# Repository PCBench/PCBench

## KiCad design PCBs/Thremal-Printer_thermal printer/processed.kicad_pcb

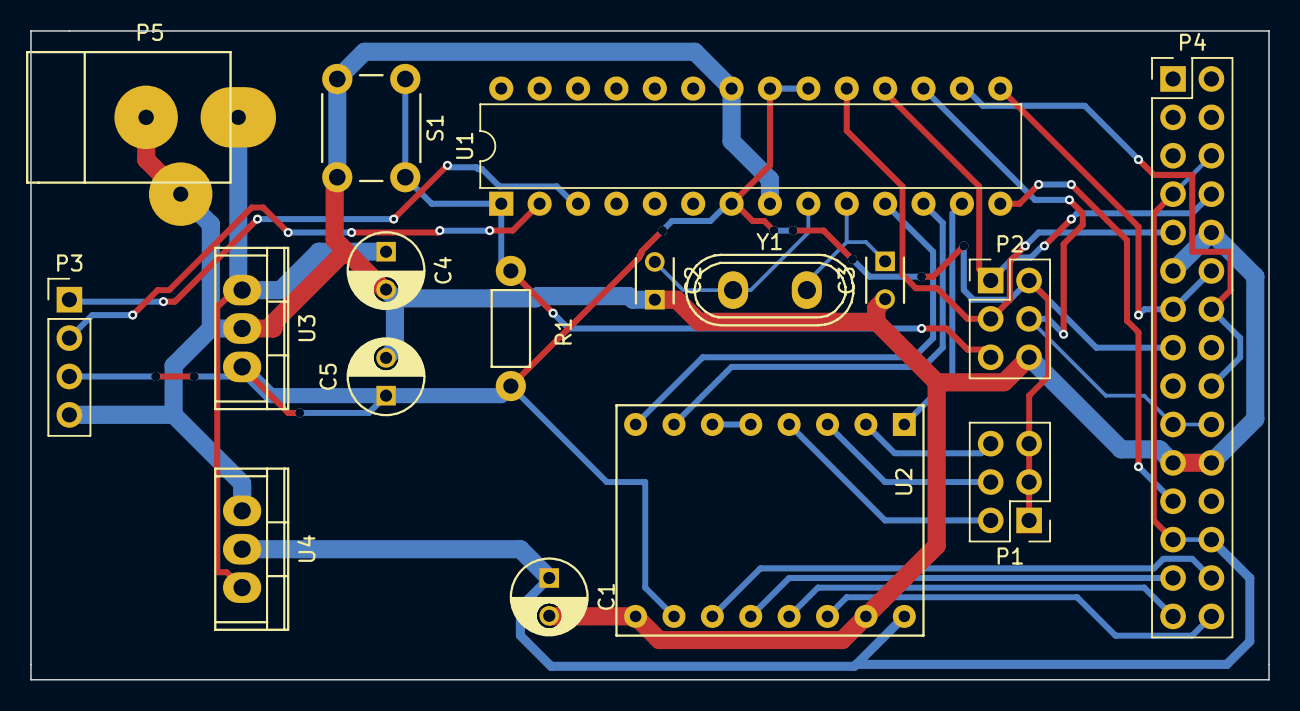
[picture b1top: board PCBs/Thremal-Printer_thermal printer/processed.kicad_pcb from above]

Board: 2 copper layers, 81.9 x 42.9 mm, 17 parts (0 on the bottom side), 26 nets.

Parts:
C1: 100uF; C_Radial_D5_L6_P2.5
C2, C3: 100nF; C_Disc_D3_P2.5
C4, C5: CP1_Small; C_Radial_D5_L6_P2.5
P1, P2: CONN_02X03; Pin_Header_Straight_2x03_Pitch2.54mm
P3: CONN_01X04; Pin_Header_Straight_1x04_Pitch2.54mm
P4: CONN_02X15; Pin_Header_Straight_2x15_Pitch2.54mm
P5: BARREL_JACK; PowerJack
R1: 10K; Resistor_Horizontal_RM7mm
S1: Switch; SW_PUSH_6mm
U1: ATMEGA328-P; DIP-28_W7.62mm
U2: A4988_pololu; SO16
U3: LM7805CT; TO-220
U4: LM317AT; TO-220
Y1: 16MHz; Crystal_HC50-U_Vertical

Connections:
/CLOCK: P2.3, P4.9, U1.19
/DATA: P2.1, P4.8, U1.18
/LATCH: P4.23, U1.14
/M1A: P4.27, U2.12
/M1B: P4.28, U2.11
/M2A: P4.29, U2.13
/M2B: P4.30, U2.14
/MOSI: P2.4, P4.19, P4.20, U1.17
/M_DIR: U1.11, U2.8
/M_ENABLE: U1.13, U2.1
/M_STEP: U1.12, U2.7
/RESET: P2.5, R1.1, S1.1, U1.1
/RX: P3.2, U1.2
/STROKE3-4: P4.14, P4.18, U1.16
/STROKE5-6: P4.12, P4.13, U1.15
/TX: P3.1, U1.3
GNDA: C1.2, C2.1, C3.2, C4.2, C5.2, P2.6, P3.4, P4.10, P4.11, P4.21, P4.22, P5.2, P5.3, S1.2, U1.8, U1.22, U2.9, U2.15, U3.2, U4.1
unnamed: C2.2, U1.9, Y1.2
unnamed: C3.1, U1.10, Y1.1
unnamed: P1.2, U2.4
unnamed: P1.4, U2.3
unnamed: P1.6, U2.2
unnamed: U2.5, U2.6
VCC: C4.1, P5.1, U3.1, U4.3
VDD: C5.1, P1.1, P1.3, P1.5, P2.2, P3.3, P4.15, R1.2, U1.7, U1.20, U1.21, U2.10, U3.3
VDDA: C1.1, P4.6, P4.7, P4.25, P4.26, U2.16, U4.2

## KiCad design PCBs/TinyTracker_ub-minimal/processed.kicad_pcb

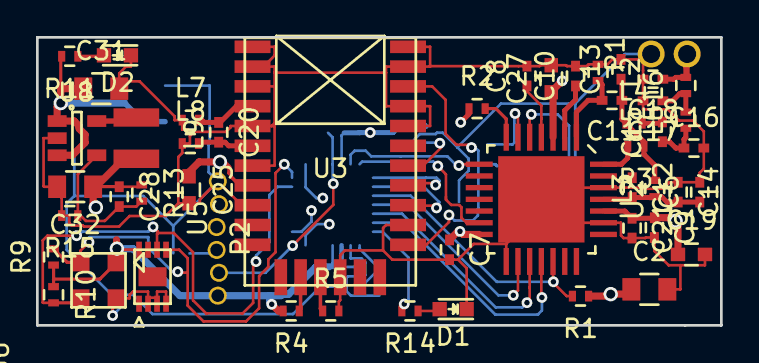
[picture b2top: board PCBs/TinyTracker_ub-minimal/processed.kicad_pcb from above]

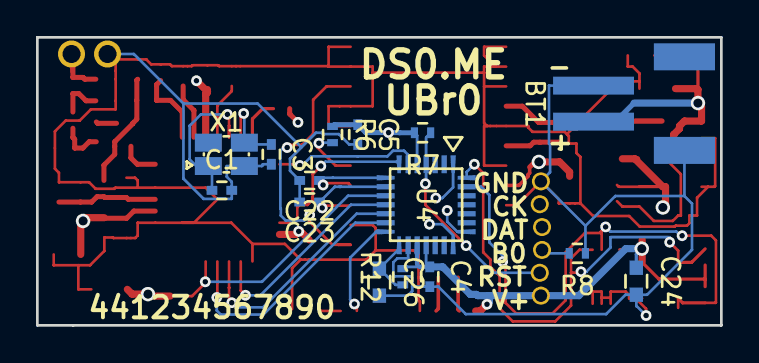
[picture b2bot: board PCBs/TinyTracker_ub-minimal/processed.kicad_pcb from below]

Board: 4 copper layers, 38.0 x 16.0 mm, 65 parts (15 on the bottom side), 42 nets.

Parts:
BT1: LiPoly; S2B-PH-SM4-TB
C1, C3: 10p; C_0402
C2, C32: 10u; C_0805
C4, C5, C7, C8, C10: 100n; C_0402
C6: 10n; C_0402
C9, C12, C15: 47p; C_0402
C11: *2.2p; C_0402
C13: 6.8p; C_0402
C14: 100p; C_0402
C16: 15p; C_0402
C17: 12p; C_0402
C18: 4.7p; C_0402
C19: 2.2u; C_0603
C20: 18p; C_0402
C21, C22, C23: 22p; C_0402
C24, C25, C26, C27: 1u; C_0603
C28: 8.2p; C_0402
C31: 4.7u; C_0805
D1: RED; LED-0603
D2: GREEN; LED-0603
L2: *18nH; R_0402
L3: 47nH; R_0402
L4: 22n; R_0402
L5: 12n; R_0402
L6: 18n; R_0402
L7, L8: DNP; R_0402
L9: 74479787222; Neosid_Inductor_SM-NE29_SMD1008
P1: ANT; ANT_50ohm
P2: CONN_01X06; 6-1.27mm
R1, R2, R4, R5, R6, R9, R10: 10k; R_0402
R3: 0; R_0402
R7, R8, R12, R15: 100k; R_0402
R11: 2.2k; R_0402
R13: 300k; R_0402
R14: 220; R_0402
U2: SX1276; QFP_28_0.65
U3: M10478; M10748
U4: STM32F048GUx; UFQFPN28
U5: CAT24M01; UDFN8
U6: MS5637
U8: LM3671; SOT-23-5
X1: 32M; XTAL-2x2.5

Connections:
+1V8: C2.1, C4.1, C5.1, C7.1, C9.1, C19.1, C21.1, C24.1, C25.1, C27.1, C28.1, C32.1, L9.2, P2.1, R1.1, R2.1, R4.2, R6.1, R7.2, R9.1, R10.1, R12.2, R13.1, U2.3, U2.14, U2.24, U3.8, U4.5, U4.17, U4.18, U5.8, U6.1
+BATT: BT1.1, C31.1, R11.2, U8.1, U8.3
/LORA TX/ANT: C18.1, L6.2, P1.2
/LORA TX/DIO0: U2.8, U4.6
/LORA TX/DIO5: U2.13, U4.7
/LORA TX/MISO: U2.17, U4.12
/LORA TX/MOSI: U2.18, U4.13
/LORA TX/SCK: U2.16, U4.11
/MCU/GPS_RX: C23.1, U3.20, U4.9
/MCU/GPS_TX: C22.1, U3.21, U4.8
/MCU/I2C_SCL: R10.2, U4.27, U5.6, U6.3
/MCU/I2C_SDA: R9.2, U4.28, U5.5, U6.2
/MCU/LORA_~CS: R1.2, U2.19, U4.10
GND: BT1.2, C1.2, C2.2, C3.2, C4.2, C5.2, C6.2, C7.2, C8.2, C9.2, C10.2, C12.1, C13.2, C14.1, C16.2, C17.2, C18.2, C19.2, C21.2, C22.2, C23.2, C24.2, C25.2, C26.2, C27.2, C31.2, C32.2, D1.1, D2.1, L2.1, L7.1, L8.1, P1.3, P2.6, R5.2, R8.1, R15.2, U2.15, U2.23, U2.26, U2.29, U3.1, U3.2, U3.3, U3.5, U3.7, U3.9, U3.15, U3.19, U3.24, U3.25, U3.27, U3.28, U4.16, U5.2, U5.3, U5.4, U6.4, U8.2, X1.3
unnamed: C1.1, U2.5, X1.1
unnamed: C3.1, U2.6, X1.2
unnamed: C8.1, U2.4
unnamed: C10.1, U2.2
unnamed: C11.1, C13.1, L3.2, L4.1, R3.1
unnamed: C11.2, L2.2, U2.1
unnamed: C6.1, C12.2, C14.2, L3.1, U2.25
unnamed: C15.1, C16.1, L5.1
unnamed: C15.2, L4.2
unnamed: C17.1, L5.2, L6.1
unnamed: C20.1, L7.2, U3.4
unnamed: C20.2, L8.2, U3.6
unnamed: C26.1, R12.1, U4.15
unnamed: C28.2, R13.2, R15.1, U8.4
unnamed: D1.2, R14.1
unnamed: D2.2, R11.1
unnamed: L9.1, U8.5
unnamed: P2.2, R7.1, U4.4
unnamed: P2.3, R8.2, U4.1
unnamed: P2.4, U4.21
unnamed: P2.5, U4.22
unnamed: R2.2, U2.7
unnamed: R3.2, U2.28
unnamed: R4.1, U3.13
unnamed: R5.1, U3.14
unnamed: R6.2, U3.22
unnamed: R14.2, U4.14
unnamed: U3.18, U3.26

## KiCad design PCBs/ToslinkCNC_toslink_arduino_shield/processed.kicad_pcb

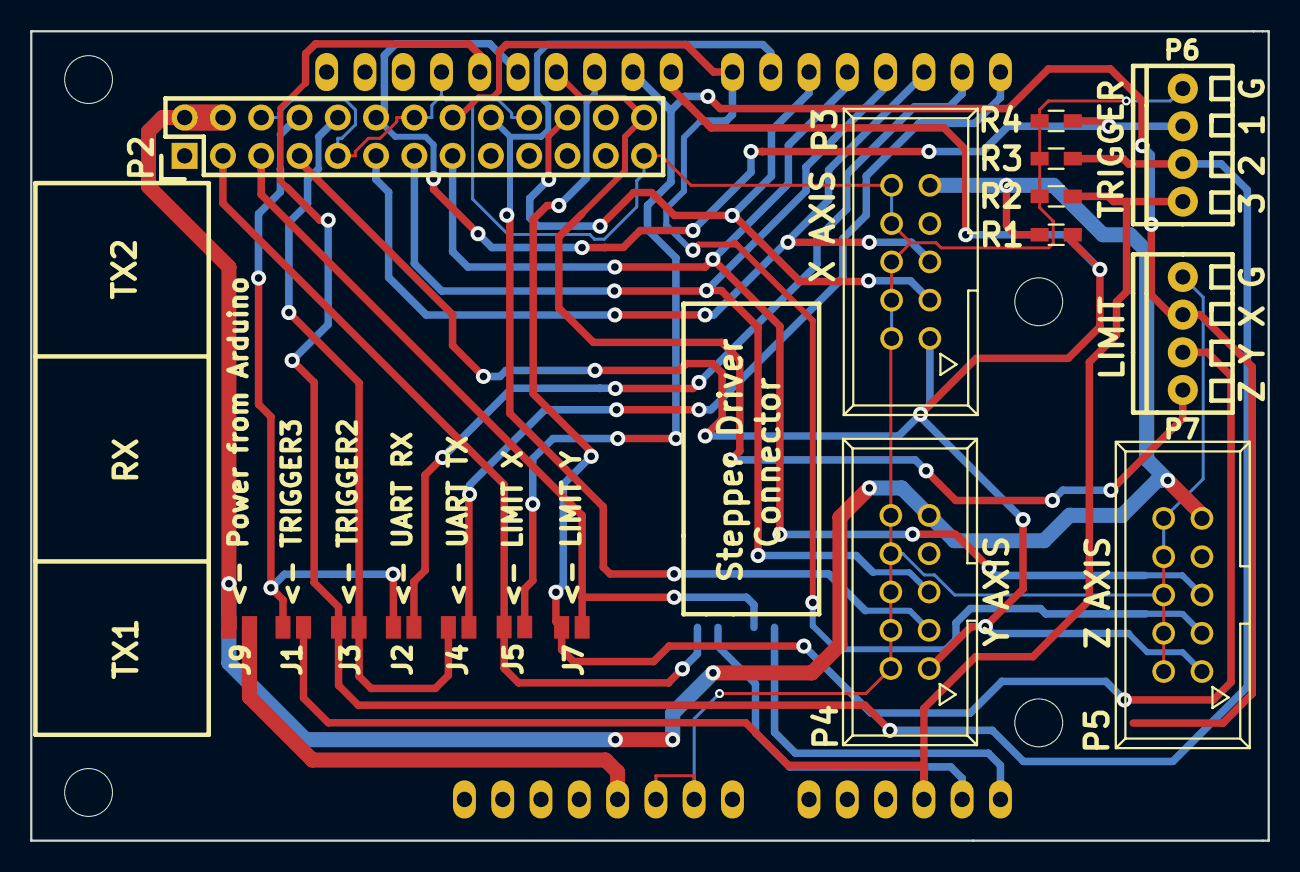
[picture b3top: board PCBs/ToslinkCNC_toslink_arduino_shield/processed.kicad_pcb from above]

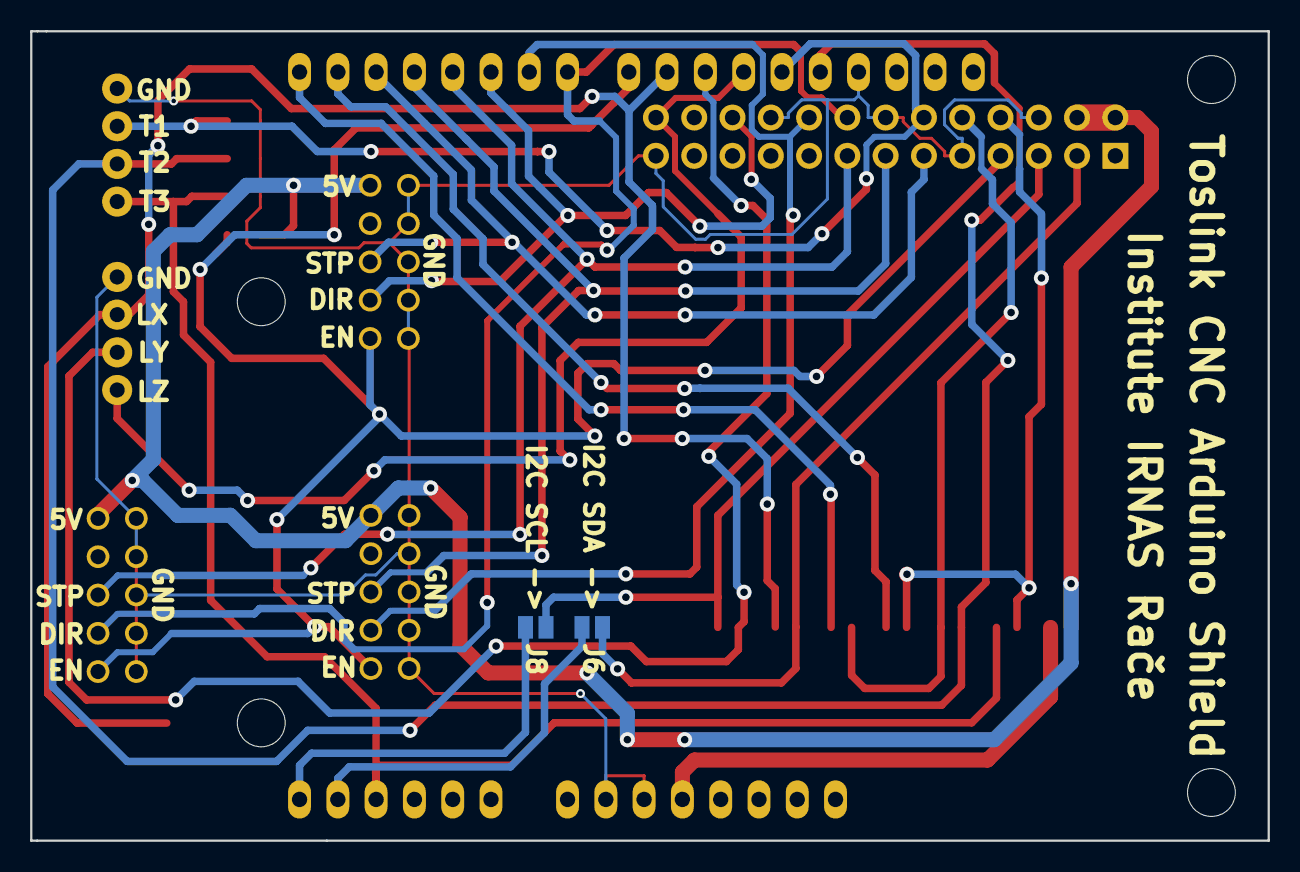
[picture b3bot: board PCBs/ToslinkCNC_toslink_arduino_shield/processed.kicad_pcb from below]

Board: 2 copper layers, 82.1 x 53.7 mm, 20 parts (2 on the bottom side), 24 nets.

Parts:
J1, J2, J3, J4, J5, J6, J7, J8, J9: solder_bridge
P1: Arduino UNO; ARDUINO_SHIELD
P2: Toslink CNC Transciever; toslink_pcb
P3, P4, P5: PoStep25-32_connector; VASCH5x2
P6, P7: CONN_01X04; terminal_block_2_5mm_4pole
R1, R2, R3, R4: 10K; R_0603_HandSoldering

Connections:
+5V: J9.2, P2.2, P2.4, P3.9, P4.9, P5.9, R1.1
DIR_X: P1.5, P2.22, P3.3
DIR_Y: P1.6, P2.18, P4.3
DIR_Z: P1.7, P2.16, P5.3
ENABLE: P1.8, P2.7, P3.1, P4.1, P5.1, R1.2
GND: P1.GND1, P1.GND2, P1.GND3, P2.6, P2.9, P2.14, P2.20, P2.25, P3.2, P3.4, P3.6, P3.8, P3.10, P4.2, P4.4, P4.6, P4.8, P4.10, P5.2, P5.4, P5.6, P5.8, P5.10, P6.4, P7.4, R2.1, R3.1, R4.1
I2C_SCL: J8.2, P1.AD5
I2C_SDA: J6.2, P1.AD4
LIMIT_X: J5.2, P1.9, P7.3
LIMIT_X/I2C_SDA: J5.1, J6.1, P2.3
LIMIT_Y: J7.2, P1.10, P7.2
LIMIT_Y/I2C_SCL: J7.1, J8.1, P2.5
LIMIT_Z: P1.11, P2.26, P7.1
POWER: J9.1, P1.5V
STEP_X: P1.2, P2.11, P3.5
STEP_Y: P1.3, P2.13, P4.5
STEP_Z: P1.4, P2.15, P5.5
TRIGGER1: P1.12, P2.12, P6.3, R4.2
TRIGGER2: J3.2, P1.13, P6.2, R3.2
TRIGGER2/UART_TX: J3.1, J4.1, P2.10
TRIGGER3: J1.2, P1.AD3, P6.1, R2.2
TRIGGER3/UART_RX: J1.1, J2.1, P2.8
UART_RX: J2.2, P1.1
UART_TX: J4.2, P1.0

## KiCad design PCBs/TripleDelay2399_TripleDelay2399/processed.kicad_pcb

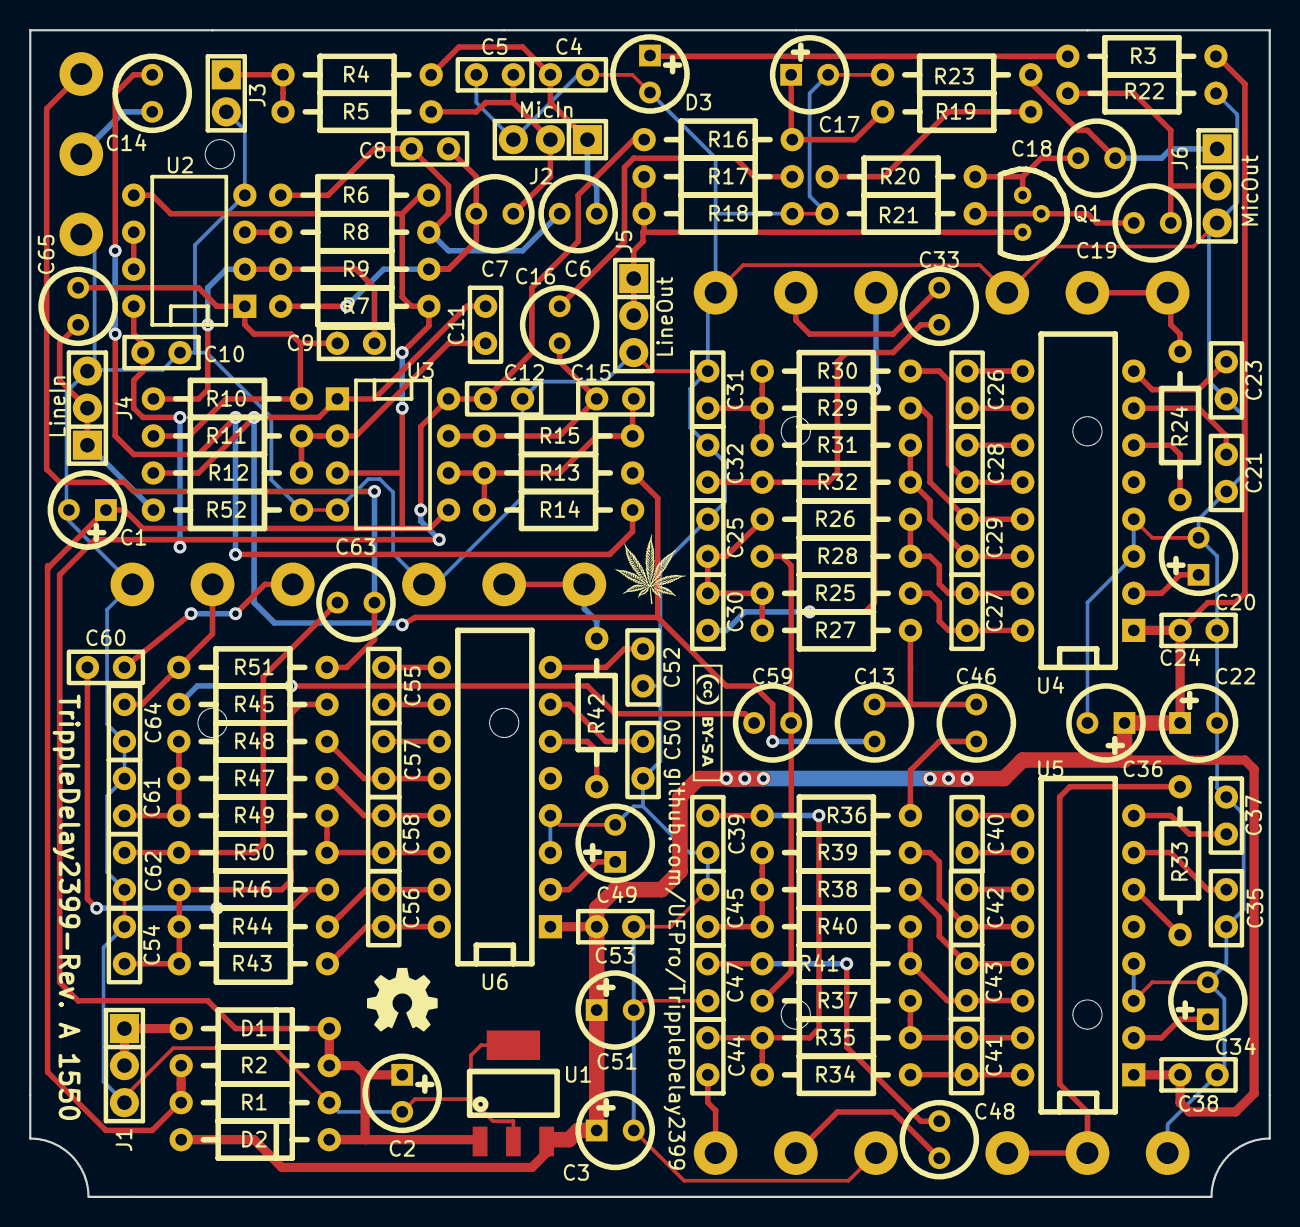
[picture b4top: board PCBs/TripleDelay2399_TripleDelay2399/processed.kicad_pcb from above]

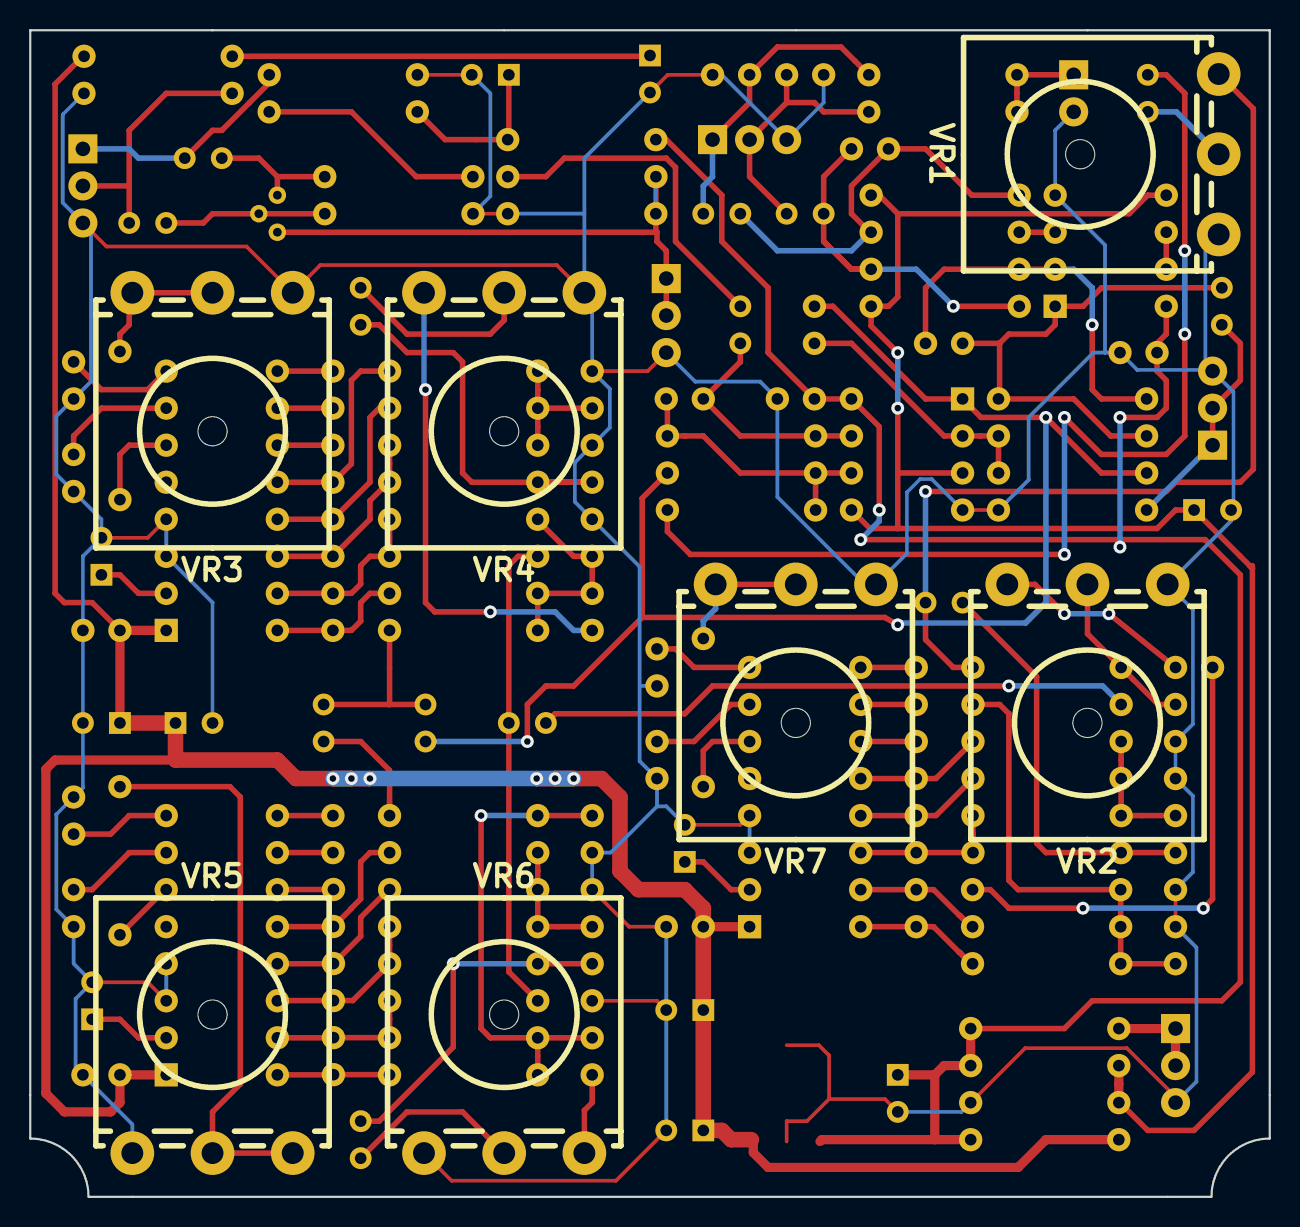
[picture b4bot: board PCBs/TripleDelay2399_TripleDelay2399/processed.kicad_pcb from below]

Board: 2 copper layers, 85.0 x 80.0 mm, 157 parts (7 on the bottom side), 90 nets.

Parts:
C1, C3, C17, C20, C22, C34, C36, C49, C51: 47µ; C_round-radial-polar-2,5mm-5mm
C2: 100µ; C_round-radial-polar-2,5mm-5mm
C4, C5: 100p; C_rect-radial-bipolar-100mil-2x5mm
C6, C7, C18, C19: 10µ; C_round-radial-bipolar-2,5mm-5mm
C8: 470p; C_rect-radial-bipolar-100mil-2x5mm
C9, C11, C15: optional; C_rect-radial-bipolar-100mil-2x5mm
C10, C12, C21, C23, C24, C26, C28, C35, C37, C38, C40, C42, C50, C52, C53, C55, C57: 100n; C_rect-radial-bipolar-100mil-2x5mm
C13, C14, C33, C46, C48, C59, C63: 1µ; C_round-radial-bipolar-2,5mm-5mm
C16: 4µ7; C_round-radial-bipolar-2,5mm-5mm
C25, C39, C54: 4n7; C_rect-radial-bipolar-100mil-2x5mm
C27, C29, C41, C43, C56, C58: 1n; C_rect-radial-bipolar-100mil-2x5mm
C30, C44, C60: 22n; C_rect-radial-bipolar-100mil-2x5mm
C31, C45, C61, C64: 47n; C_rect-radial-bipolar-100mil-2x5mm
C32, C47, C62: 10n; C_rect-radial-bipolar-100mil-2x5mm
C65: optional; C_round-radial-bipolar-2,5mm-5mm
D1, D2: 1N4001; D_axial_400mil
D3: blue; C_round-radial-polar-2,5mm-5mm
Des*: Val*; Pad-TH-0,8mm-1,6mm
Des*_2, Des*_3, Des*_4, Des*_5, Des*_6, Des*_7, Des*_8: Val*; MountingHole-3,2mm
Des*_9, Des*_10, Des*_11, Des*_12, Des*_13, Des*_14: Val*; Pad-TH-0,8mm-1,6mm
J1: DCIn; PinArray-100mil-1x3
J2: MicIn; PinArray-100mil-1x3
J3: P48; PinArray-100mil-1x2
J4: LineIn; PinArray-100mil-1x3
J5: LineOut; PinArray-100mil-1x3
J6: MicOut; PinArray-100mil-1x3
Q1: J112; TO-92_staggered-narrow
R1, R2, R8, R9, R11, R18, R25, R26, R27, R29, R30, R34, R35, R36, R38, R39, R43, R44, R45, R47, R48: 10k; R_axial_400mil
R3, R16, R32, R41, R50: 1k; R_axial_400mil
R4, R5, R22, R23: 6k8; R_axial_400mil
R6, R7: 4k7; R_axial_400mil
R10, R12: 180k; R_axial_400mil
R13, R14: 39k; R_axial_400mil
R15: 910; R_axial_400mil
R17, R21: 100k; R_axial_400mil
R19: 56k; R_axial_400mil
R20: 43k; R_axial_400mil
R24, R33, R42: 2k7; R_axial_400mil
R28, R37, R46: 5k1; R_axial_400mil
R31, R40, R49: 20k; R_axial_400mil
R51: 2k; R_axial_400mil
R52: optional; R_axial_400mil
U1: MCP1755S-5002; SOT223-3
U2, U3: NE5532; DIP-8_300
U4, U5, U6: PT2399; DIP-16_300
VAL: REF; CC-BY-SA08mm
VAL_2: REF; hempleaf5mm.mod
VAL_3: REF; oshw5mm
VR1, VR2, VR3, VR4, VR5, VR6, VR7: 50k lin; VR_potentiometer-piher-topmount_narrow-pins

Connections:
+4V5: C1.1, R1.1, R2.1, R6.1, R7.1, U2.5, U3.3, U3.5
+5V: C3.1, C22.1, C24.2, C36.1, C38.2, C51.1, C53.2, D2.1, R3.1, U1.3, U4.1, U5.1, U6.1
+9V: C2.1, C10.1, C12.1, D1.2, D2.2, R2.2, R16.1, U1.1, U2.8, U3.8
DLY_A-B: C59.2, R28.2, R37.2
DRY: C13.2, C46.2, R27.2
GND: C1.2, C2.2, C3.2, C4.2, C5.2, C10.2, C12.2, C17.2, C20.2, C21.2, C22.2, C23.2, C24.1, C25.2, C31.2, C32.2, C34.2, C35.2, C36.2, C37.2, C38.1, C39.2, C45.2, C47.2, C49.2, C50.2, C51.2, C52.2, C53.1, C54.2, C61.2, C62.2, C64.2, D3.2, J1.3, J2.3, J3.2, J4.3, J5.3, J6.3, R1.2, R18.2, R21.2, R22.2, R23.2, R52.2, U1.2, U1.4, U2.4, U3.4, U4.3, U4.4, U5.3, U5.4, U6.3, U6.4, VR1.1, VR2.1, VR3.1, VR4.1, VR5.1, VR6.1, VR7.1
unnamed: C14.2, VR1.2
unnamed: C14.1, R14.1
unnamed: C15.1, R13.2, R14.2, R15.1, U3.6
unnamed: C15.2, C16.1, R15.2, U3.7
unnamed: C6.2, C8.1, R6.2, R8.1
unnamed: C7.2, C8.2, R7.2, R9.1
unnamed: R8.2, U2.3
unnamed: C9.1, R9.2, R10.1, U2.2
unnamed: C9.2, C65.2, R10.2, R11.1, U2.1
unnamed: D3.1, R3.2
unnamed: C25.1, C30.1, R25.1, R26.1, R27.1
unnamed: C30.2, VR4.3
unnamed: C16.2, R17.1
unnamed: C18.1, Q1.1, R20.2
unnamed: C19.1, Q1.2, R21.1
unnamed: D1.1, J1.1, J1.2
unnamed: C62.1, C63.1, R50.2
unnamed: C56.1, R43.2, U6.16
unnamed: C58.2, R47.1, U6.13
unnamed: C58.1, R49.1, R50.1, U6.14
unnamed: C61.1, R47.2, R48.2, R49.2
unnamed: C64.1, R51.2, VR2.2
unnamed: C60.2, VR2.3
unnamed: C57.2, R48.1, U6.12
unnamed: C55.1, U6.9
unnamed: C55.2, U6.10
unnamed: C57.1, U6.11
unnamed: C60.1, R46.2
unnamed: C56.2, R44.2, U6.15
unnamed: R42.2, VR7.2, VR7.3
unnamed: R42.1, U6.6
unnamed: C4.1, C6.1, J2.1, R4.2
unnamed: C5.1, C7.1, J2.2, R5.2
unnamed: C50.1, U6.7
unnamed: C54.1, R43.1, R44.1, R45.1, R46.1
unnamed: C59.1, R45.2
unnamed: C49.1, U6.2
unnamed: C52.1, U6.8
unnamed: R19.2, R20.1
unnamed: J5.1, J5.2, Q1.3, R17.2, R18.1
unnamed: C17.1, R16.2, R19.1
unnamed: C18.2, J6.1, R23.1
unnamed: C19.2, J6.2, R22.1
unnamed: U2.6, U2.7
unnamed: C65.1, J4.1, J4.2, R52.1
unnamed: C11.1, R11.2, R12.1, U3.2
unnamed: C11.2, C13.1, R12.2, R13.1, U3.1
unnamed: C47.1, C48.1, R41.2
unnamed: C43.2, R38.1, U5.13
unnamed: C43.1, R40.1, R41.1, U5.14
unnamed: C45.1, R38.2, R39.2, R40.2
unnamed: C41.1, R34.2, U5.16
unnamed: C46.1, R36.2
unnamed: C34.1, U5.2
unnamed: C35.1, U5.7
unnamed: C42.2, R39.1, U5.12
unnamed: C33.2, VR4.2
unnamed: C40.1, U5.9
unnamed: C40.2, U5.10
unnamed: C42.1, U5.11
unnamed: C37.1, U5.8
unnamed: C41.2, R35.2, R37.1, U5.15
unnamed: C39.1, C44.1, R34.1, R35.1, R36.1
unnamed: C44.2, VR6.3
unnamed: C48.2, VR6.2
unnamed: J3.1, R4.1, R5.1
unnamed: R33.2, VR5.2, VR5.3
unnamed: R33.1, U5.6
unnamed: C32.1, C33.1, R32.2
unnamed: C21.1, U4.7
unnamed: C20.1, U4.2
unnamed: R24.1, U4.6
unnamed: C23.1, U4.8
unnamed: C26.1, U4.9
unnamed: C26.2, U4.10
unnamed: C28.1, U4.11
unnamed: C29.1, R31.1, R32.1, U4.14
unnamed: C29.2, R29.1, U4.13
unnamed: C27.2, R26.2, R28.1, U4.15
unnamed: C28.2, R30.1, U4.12
unnamed: C31.1, R29.2, R30.2, R31.2
unnamed: R24.2, VR3.2, VR3.3
unnamed: C27.1, R25.2, U4.16
WET: C63.2, R51.1, VR1.3

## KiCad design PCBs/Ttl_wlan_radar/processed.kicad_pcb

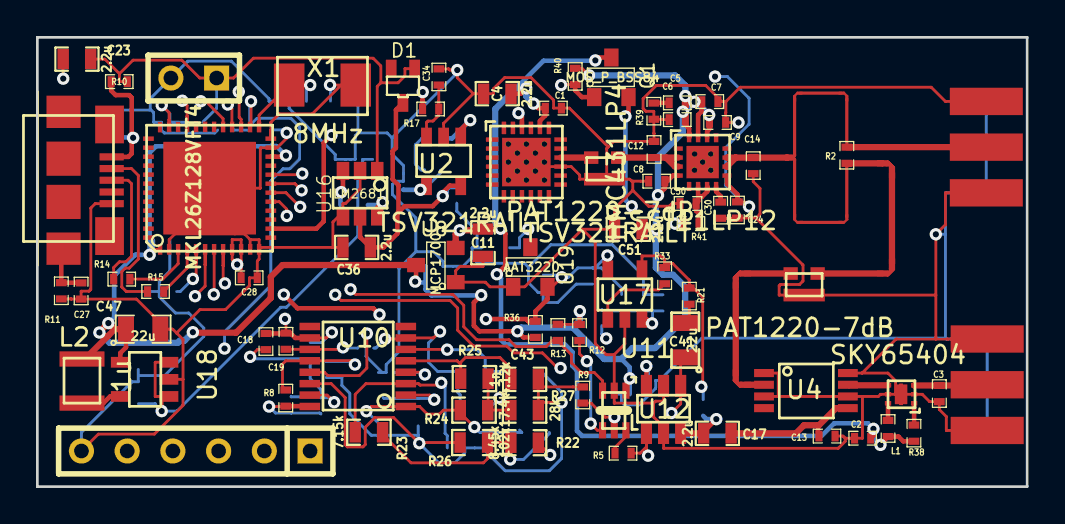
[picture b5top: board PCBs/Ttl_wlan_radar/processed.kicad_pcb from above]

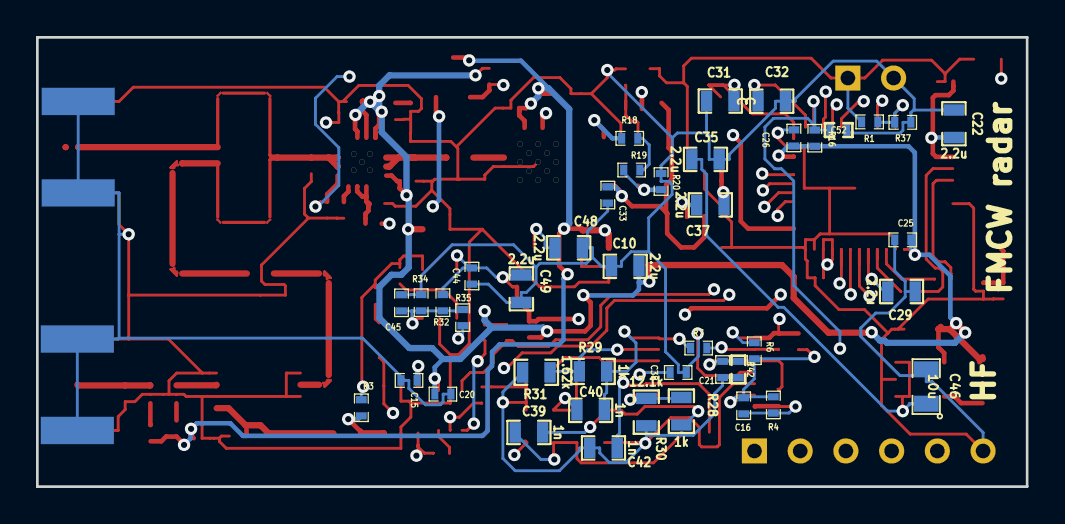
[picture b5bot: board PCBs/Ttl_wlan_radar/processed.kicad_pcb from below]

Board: 4 copper layers, 55.0 x 25.0 mm, 128 parts (42 on the bottom side), 75 nets.

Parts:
C1: 10n; SM0402_c
C2: 100n; SM0402_c
C3: 0.5p; SM0402_c
C4, C10, C11, C17, C22, C23, C29, C35, C36, C37, C48, C49, C51: 2.2u; SMD-0603_c
C5: 3.3p; SMD-0402_c
C6, C7, C8, C15, C20, C25, C26, C28, C33, C34, C38, C44, C45, C52: 100n; SMD-0402_c
C9: 1.8p; SMD-0402_c
C12: 0.3p; SMD-0402_c
C13: 100p; SM0402_c
C14: 0.5p; SMD-0402_c
C16, C18, C19, C21, C24, C30: 10p; SMD-0402_c
C27: 4.7n; SMD-0402_c
C31, C32: C; SMD-0603_c
C39, C40, C42, C43: 1n; SMD-0603_c
C41, C47: 22u; SMD-0805
C46: 10u; SMD-0805
C50: 100p; SMD-0402_c
D1: BAS40WT; SOT-323
F1, F2, F3, F4: CORNER; miter_0.179_90deg
F5, F6, F7, F8: CORNER; MITER_0.350mm_90deg
L1: 0.6n; SM0402
L2: 1u; L2520
P1, P2: CONN_2; CONSMA003.062
P3: CONN_2; SIL-2
P4: CONN_6; SIL-6
Q1: MOS_P_BSS84; SOT-23
R1, R16, R32, R34, R37, R40: 47k; SMD-0402_r
R2, R17, R38: 100; SMD-0402_r
R3: 4.7k; SMD-0402_r
R4, R6: 4.99k; SMD-0402_r
R5, R33: 1k; SMD-0402_r
R7, R8, R42: 200k; SMD-0402_r
R9: 1.5k; SMD-0402_r
R10, R41: 0; SMD-0402_r
R11: 1M; SMD-0402_r
R12, R13, R18, R19, R20: 10k; SMD-0402_r
R14, R15: 33; SMD-0402_r
R21: 50; SMD-0402_r
R22: 8.45k; SMD-0603_r
R23: 7.15k; SMD-0603_r
R24: 17.4k; SMD-0603_r
R25: 4.12k; SMD-0603_r
R26: 102k; SMD-0603_r
R27: 28k; SMD-0603_r
R28, R29: 1k; SMD-0603_r
R30: 12.1k; SMD-0603_r
R31: 1.62k; SMD-0603_r
R35, R36: NOP; SMD-0402_r
R39: 25; SMD-0402_r
U1: SST11LP12; VQFN-16
U2: HMC431LP4; VQFN-24
U3: SKY65404; XFDFN-6
U4: HMC219AMS8; MSOP-8
U5, U7: PAT1220-7dB; PAT1220
U8: MCP1700; SOT23
U10: LTC6242; SSOP-16
U11: LT6230; TSOT-23
U12: MCP4017; SC-70-6
U13: USB-MICRO; USB_MICRO
U14: MKL26Z128VFT4; QFN-48-1EP
U15, U17: TSV321RAILT; SOT-23-5
U16: LM2681; SOT-23-6
U18: SC189; SOT-23-5
U19: AAT3220; SOT-23
X1: 8MHz; XTAL-7A

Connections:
/3V0: C1.1, C2.1, C4.1, C11.1, L1.2, Q1.3, R38.2, U2.20, U8.2
/10V: C33.1, C36.1, D1.3, U15.5, U16.5
/DET_REF: C30.1, U1.8
/IF: C13.1, C17.2, U4.5
/PA_RFOUT: C14.1, F1.1, F3.2, U1.10, U1.11
/VG: C21.2, C42.2, C43.2, R3.1, R9.2, R21.2, R26.2, R27.1, R30.2, R31.2, R33.1, R35.1, R42.2, U10.14, U17.4
/VTUNE: R18.2, U2.22, U15.1
/mcu/3V3: C5.1, C6.1, C7.1, C8.1, C9.1, C10.1, C20.1, C25.1, C26.1, C47.1, C51.1, L2.2, R12.1, R13.1, R16.2, R36.2, R40.1, U1.4, U1.14, U1.15, U1.16, U8.3, U12.1, U14.1, U14.22, U18.4
/mcu/3V3A: C15.1, C28.1, C38.1, C44.1, C49.1, R32.1, R36.1, U10.4, U11.6, U14.9, U14.10, U17.5, U19.2
/mcu/5V: C23.1, C35.1, C46.1, C48.1, D1.1, P3.1, R1.1, R10.1, U16.1, U18.1, U18.3, U19.3
/mcu/ADC_DM: C18.2, C19.1, R6.2, U10.10, U14.8
/mcu/ADC_DP: C16.1, R4.1, R8.1, U10.16, U14.7
/mcu/DAC_OUT: R17.2, U14.14
/mcu/I2C_SCL: R13.2, U12.3, U14.27
/mcu/I2C_SDA: R12.2, U12.4, U14.28
/mcu/PA_DET: C24.1, U1.9, U14.33
/mcu/PA_EN: Q1.1, R40.2, U14.29
/mcu/SWD_CLK: P4.1, U14.17
/mcu/SWD_DIO: P4.2, U14.20
/mcu/UART_RX: P4.4, U14.18
/mcu/UART_TX: P4.5, U14.19
/mcu/USBM: R15.2, U13.2
/mcu/USBP: R14.2, U13.3
/mcu/VBUS: C22.1, R10.2, U13.1, U14.6
/mcu/~RESET: C52.1, P4.3, R16.1, U14.26
GND: C1.2, C2.2, C3.2, C4.2, C6.2, C7.2, C8.2, C9.2, C10.2, C11.2, C12.2, C13.2, C14.2, C15.2, C20.2, C22.2, C23.2, C24.2, C25.2, C26.2, C27.2, C28.2, C29.2, C30.2, C31.2, C32.2, C33.2, C34.2, C35.2, C36.2, C38.2, C44.2, C45.2, C46.2, C47.2, C48.2, C49.2, C50.2, C51.2, C52.2, P1.2, P2.2, P3.2, P4.6, R11.2, R20.1, R34.2, R37.2, R39.1, U1.PAD, U2.15, U2.PAD, U3.2, U3.5, U3.PAD, U4.1, U4.3, U4.6, U4.8, U5.3, U7.3, U8.1, U10.13, U11.2, U11.5, U12.2, U13.5, U14.2, U14.11, U14.12, U14.23, U14.49, U15.2, U16.2, U16.4, U17.2, U18.2, U19.1
unnamed: C3.1, P2.1, U3.3
unnamed: C5.2, R39.2
unnamed: C12.1, U1.2, U1.3, U5.2
unnamed: C16.2, C18.1, R4.2, R6.1, U10.15
unnamed: C17.1, R3.2, U11.3
unnamed: C19.2, R7.1, U10.11
unnamed: C21.1, R8.2, R42.1, U10.12
unnamed: C27.1, R11.1, U13.SH
unnamed: C29.1, U14.5
unnamed: C31.1, U14.24, X1.2
unnamed: C32.1, U14.25, X1.1
unnamed: C34.1, R17.1, U15.3
unnamed: C37.1, U16.6
unnamed: C37.2, U16.3
unnamed: C39.1, R24.2, R28.1, U10.1
unnamed: C39.2, R22.1, R23.2, R26.1
unnamed: C40.1, R7.2, R29.1, U10.7
unnamed: C40.2, R24.1, R25.1, R27.2
unnamed: C41.1, R9.1, U11.4, U12.5
unnamed: C41.2, R21.1
unnamed: C42.1, R23.1, U10.3
unnamed: C43.1, R25.2, U10.5
unnamed: C45.1, R32.2, R34.1, R35.2, U17.3
unnamed: C50.1, R41.1, U1.6, U1.7
unnamed: F1.2, F2.1
unnamed: F2.2, P1.1, R2.1
unnamed: F3.1, F4.2
unnamed: F4.1, F5.1, R2.2
unnamed: F5.2, F6.1
unnamed: F6.2, U7.2
unnamed: F7.1, F8.2
unnamed: F7.2, U7.1
unnamed: F8.1, U4.2
unnamed: L1.1, U3.6
unnamed: L2.1, U18.5
unnamed: Q1.2, R41.2
unnamed: R1.2, R37.1, U14.35
unnamed: R5.2, U12.6
unnamed: R14.1, U14.3
unnamed: R15.1, U14.4
unnamed: R18.1, R19.1
unnamed: R19.2, R20.2, U15.4
unnamed: R5.1, R22.2, U11.1
unnamed: R28.2, R30.1, U10.2
unnamed: R29.2, R31.1, U10.6
unnamed: R33.2, U17.1
unnamed: R38.1, U3.1
unnamed: U2.16, U5.1
unnamed: U3.4, U4.7

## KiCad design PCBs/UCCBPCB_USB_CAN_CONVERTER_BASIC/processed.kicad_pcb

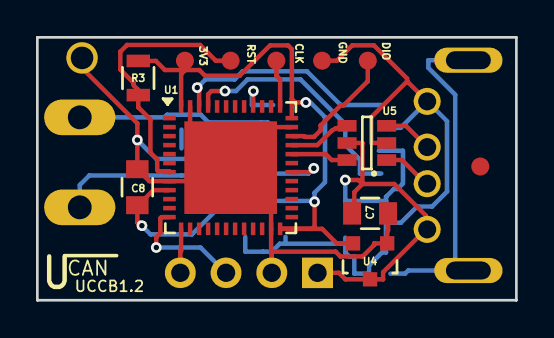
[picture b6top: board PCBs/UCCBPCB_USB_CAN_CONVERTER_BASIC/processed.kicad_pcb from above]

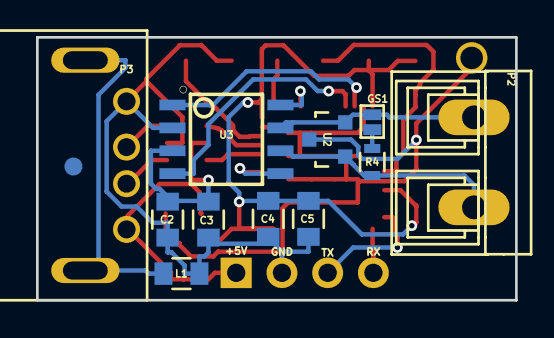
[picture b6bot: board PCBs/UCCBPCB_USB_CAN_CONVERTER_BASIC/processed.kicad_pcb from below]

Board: 2 copper layers, 26.6 x 14.6 mm, 21 parts (11 on the bottom side), 20 nets.

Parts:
C2, C5: 100n; C_0805
C3, C4: 10n; C_0805
C7, C8: 1u; C_0805
F1: fiducial; Fiducial_1mm_Dia_2.54mm_Outer_CopperTop
F2: fiducial; Fiducial_1mm_Dia_2.54mm_Outer_CopperBottom
GS1: GS2; GS2s
L1: 30R@100MHz; C_0805
P1: CONN_01X05; swd_smd_conn5
P2: CONN_01X02; AK300-2MIRROR
P3: USB_A; USB_A_DS1097R
P4: CONN_01X04; Pin_Header_Angled_1x04m
R3: 10k; R_0805
R4: 120R; R_0603
U1: STM32F042C6Ux; QFN-48-1EP_7x7mm_Pitch0.5mm
U2: PESD2CAN; SOT-23
U3: TCAN332; SO
U4: MCP1700T-3302E/TT; SOT-23
U5: USBLC6-2SC6; SOT-23-6

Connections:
+3V3: C4.1, C5.1, C8.1, P1.1, R3.2, U1.9, U1.24, U1.36, U1.48, U4.2
+5V: C2.1, C3.1, C7.1, P3.1, P4.1, U3.3, U4.3, U5.5
/USART_RX: P4.4, U1.13
/USART_TX: P4.3, U1.12
CAN_MOD: U1.40, U3.8
CAN_MOD2: U1.30, U3.5
CAN_RX: U1.45, U3.4
CAN_TX: U1.46, U3.1
GND: C2.2, C3.2, C4.2, C5.2, C7.2, C8.2, L1.1, P1.4, P3.4, P4.2, U1.8, U1.23, U1.35, U1.47, U1.49, U2.3, U3.2, U4.1, U5.2
unnamed: GS1.1, R4.1
unnamed: GS1.2, P2.2, U2.2, U3.7
unnamed: L1.2, P3.5
unnamed: P1.2, R3.1, U1.7
unnamed: P2.1, R4.2, U2.1, U3.6
unnamed: P3.2, U5.1
unnamed: P3.3, U5.3
unnamed: U1.32, U5.6
unnamed: U1.33, U5.4
SW_CLK: P1.3, U1.37
SW_DIO: P1.5, U1.34

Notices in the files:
PCBs/TripleDelay2399_TripleDelay2399/processed.kicad_pcb:
Licence: CC-BY-SA
